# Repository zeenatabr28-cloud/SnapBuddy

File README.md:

# SnapBuddy
A retro 80's inspired Camera

WHY?
I want to be able to document Fallen and I can't actually affford a camera... So I am making one!

WHAT?
A cute retro style camera, with small touches that make it more personal/customisable, that only takes grainy, retro looking photos.

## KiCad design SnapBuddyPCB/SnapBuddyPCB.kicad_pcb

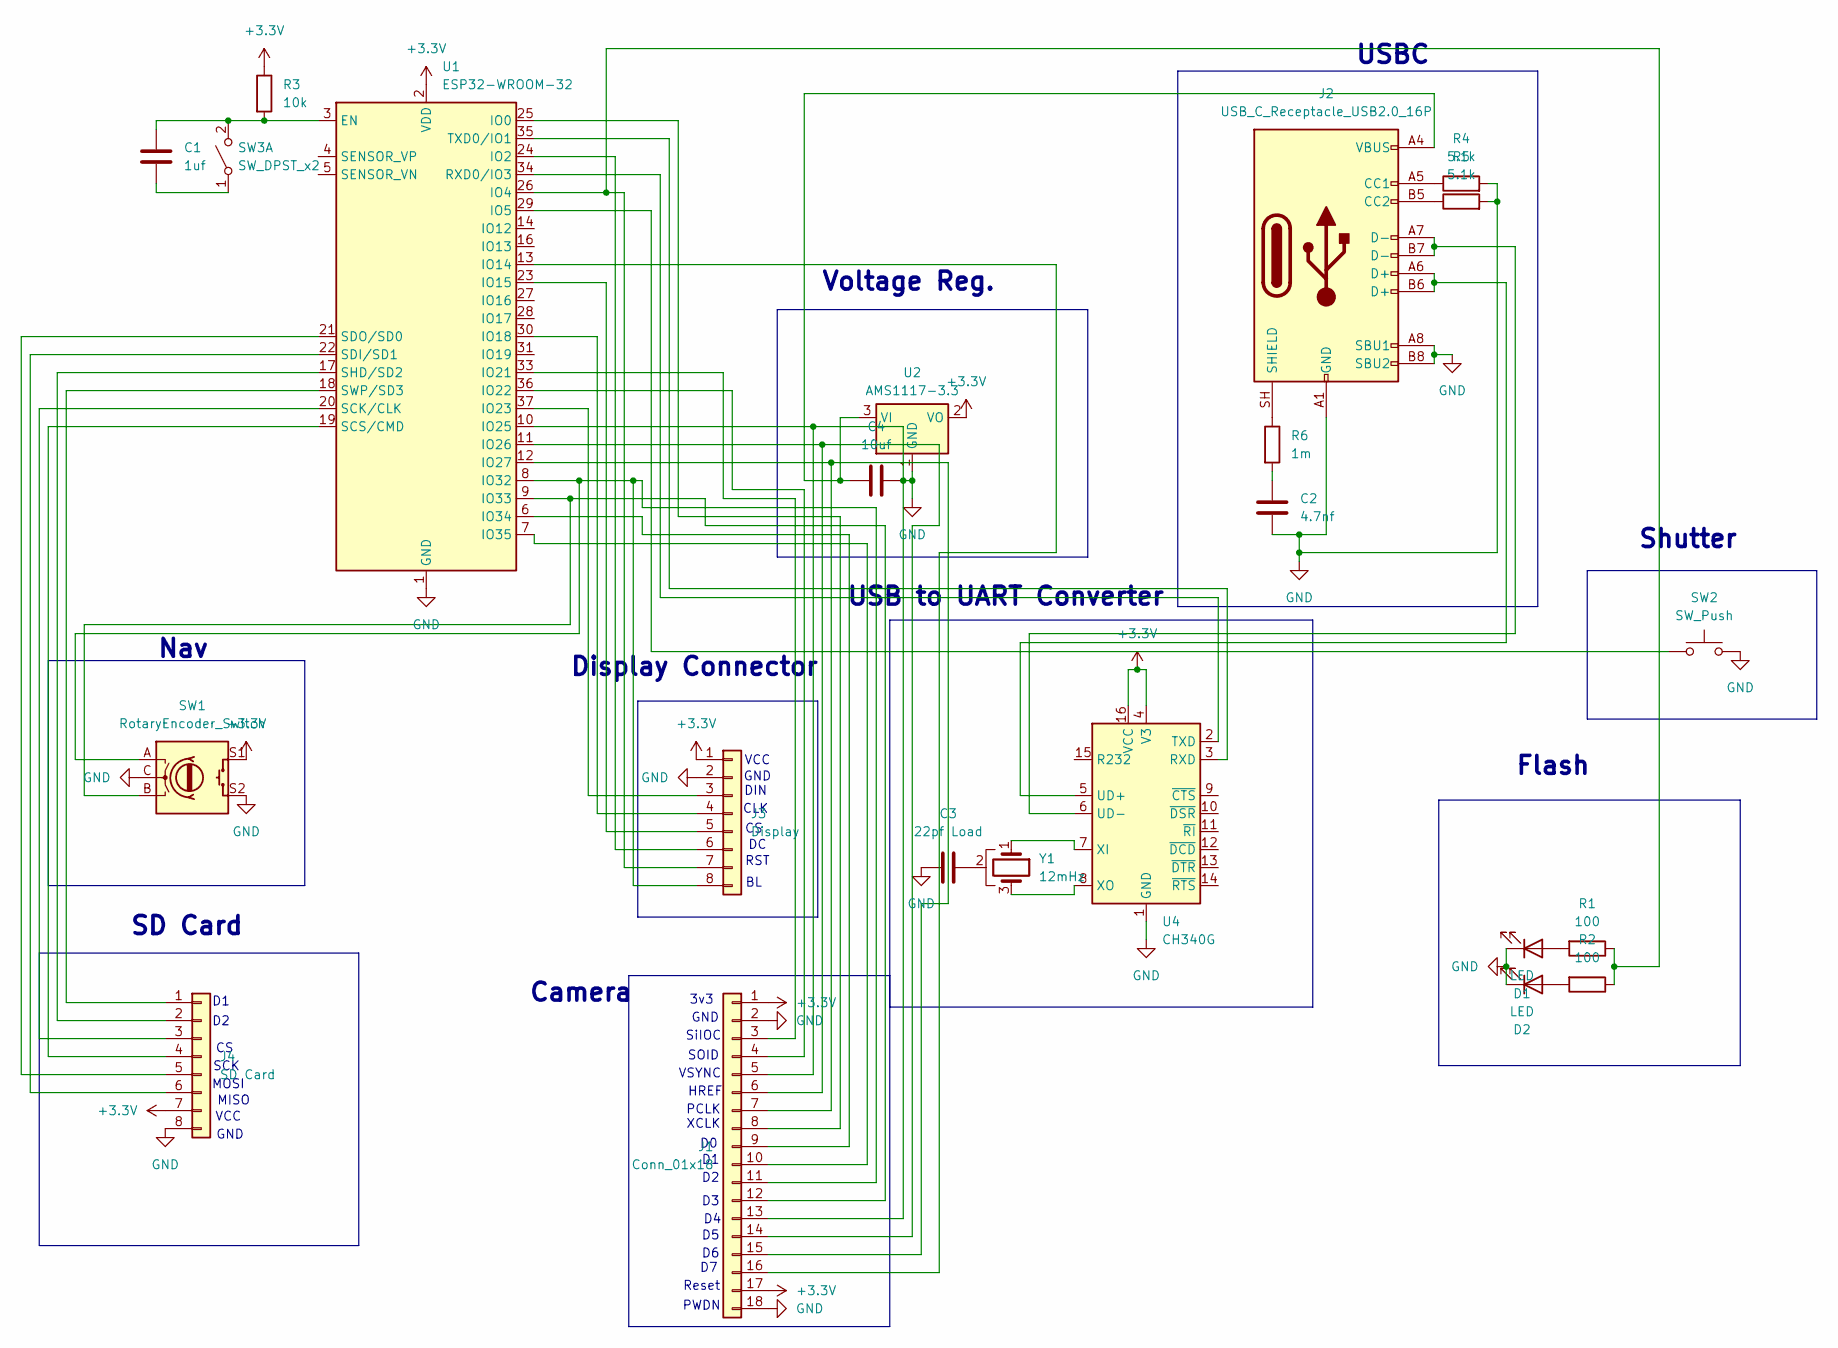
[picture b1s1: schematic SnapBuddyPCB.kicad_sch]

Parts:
C1: 1uf; CP_Elec_3x5.3
C2: 4.7nf; CP_Elec_3x5.3
C3: 22pf Load; CP_Elec_3x5.3
C4: 10uf; CP_Elec_3x5.3
D1, D2: LED; LED_D3.0mm
J1: Conn_01x18; PinSocket_1x18_P1.27mm_Vertical_SMD_Pin1Left
J2: USB_C_Receptacle_USB2.0_16P; USB_C_Receptacle_XKB_U262-16XN-4BVC11
J3: Display; PinSocket_1x08_P2.54mm_Vertical
J4: SD Card; PinSocket_1x08_P2.54mm_Vertical
R1, R2: 100; R_0603_1608Metric_Pad0.98x0.95mm_HandSolder
R3: 10k; R_0603_1608Metric_Pad0.98x0.95mm_HandSolder
R4, R5: 5.1k; R_0603_1608Metric_Pad0.98x0.95mm_HandSolder
R6: 1m; R_0603_1608Metric_Pad0.98x0.95mm_HandSolder
SW1: RotaryEncoder_Switch; RotaryEncoder_Bourns_Horizontal_PEC09-2xxxF-Sxxxx
SW2: SW_Push; SW_Push_1P1T_NO_CK_PTS125Sx85PSMTR
SW3: SW_DPST_x2; SW_Push_1P1T_NO_CK_PTS125Sx85PSMTR
U1: ESP32-WROOM-32
U2: AMS1117-3.3; SOT-223-3_TabPin2
U4: CH340G; SOIC-16_3.9x9.9mm_P1.27mm
Y1: 12mHz; Crystal_HC52-U-3Pin_Vertical

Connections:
+3.3V: J1.1, J1.17, J3.1, J4.7, R3.1, SW1.S1, U1.2 (VDD), U2.2 (VO), U4.4 (V3), U4.16 (VCC)
GND: C2.2, C3.2, C4.2, D1.1 (K), D2.1 (K), J1.2, J1.5, J1.13, J1.18, J2.A1 (GND), J2.A8 (SBU1), J2.A12 (GND), J2.B1 (GND), J2.B8 (SBU2), J2.B12 (GND), J3.2, J4.8, R4.2, R5.2, SW1.C, SW1.S2, SW2.2, U1.1 (GND), U1.10 (IO25), U1.15 (GND), U1.38 (GND), U1.39 (GND), U2.1 (GND), U4.1 (GND)
unnamed: C2.1, R6.2
unnamed: C3.1, Y1.2
unnamed: D1.2 (A), R1.2
unnamed: D2.2 (A), R2.2
unnamed: J1.3, U1.33 (IO21)
unnamed: J1.4, U1.36 (IO22)
unnamed: J1.8, U1.25 (IO0)
unnamed: J1.9, U1.6 (IO34)
unnamed: J1.10, U1.7 (IO35)
unnamed: J1.11, J3.8, SW1.A, U1.8 (IO32)
unnamed: J1.12, SW1.B, U1.9 (IO33)
unnamed: J1.6, J1.14, U1.11 (IO26)
unnamed: J1.7, J1.15, U1.12 (IO27)
unnamed: J1.16, U1.13 (IO14)
unnamed: J2.A5 (CC1), R4.1
unnamed: J2.B5 (CC2), R5.1
unnamed: J2.SH (SHIELD), R6.1
unnamed: J3.3, U1.37 (IO23)
unnamed: J3.4, U1.30 (IO18)
unnamed: J3.5, U1.23 (IO15)
unnamed: J3.6, U1.24 (IO2)
unnamed: J3.7, R1.1, R2.1, U1.26 (IO4)
unnamed: J4.1, U1.18 (SWP/SD3)
unnamed: J4.2, U1.17 (SHD/SD2)
unnamed: J4.3, U1.20 (SCK/CLK)
unnamed: J4.4, U1.19 (SCS/CMD)
unnamed: J4.5, U1.21 (SDO/SD0)
unnamed: J4.6, U1.22 (SDI/SD1)
unnamed: C1.2, SW3.1 (A)
unnamed: C1.1, R3.2, SW3.2 (B), U1.3 (EN)
unnamed: SW2.1, U1.29 (IO5)
unnamed: U1.34 (RXD0/IO3), U4.2 (TXD)
unnamed: U1.35 (TXD0/IO1), U4.3 (RXD)
unnamed: C4.1, J2.A4 (VBUS), J2.A9 (VBUS), J2.B4 (VBUS), J2.B9 (VBUS), U2.3 (VI)
unnamed: J2.A6 (D+), J2.B6 (D+), U4.5 (UD+)
unnamed: J2.A7 (D-), J2.B7 (D-), U4.6 (UD-)
unnamed: U4.7 (XI), Y1.1
unnamed: U4.8 (XO), Y1.3

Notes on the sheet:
Reset
VCC
GND
Camera
USBC
XCLK
DIN
CLK
MOSI
Nav
PWDN
RST
HREF
SOID
Flash
Display Connector
SD Card
VSYNC
SiIOC
MISO
3v3
SCK
PCLK
Shutter
USB to UART Converter
Voltage Reg.

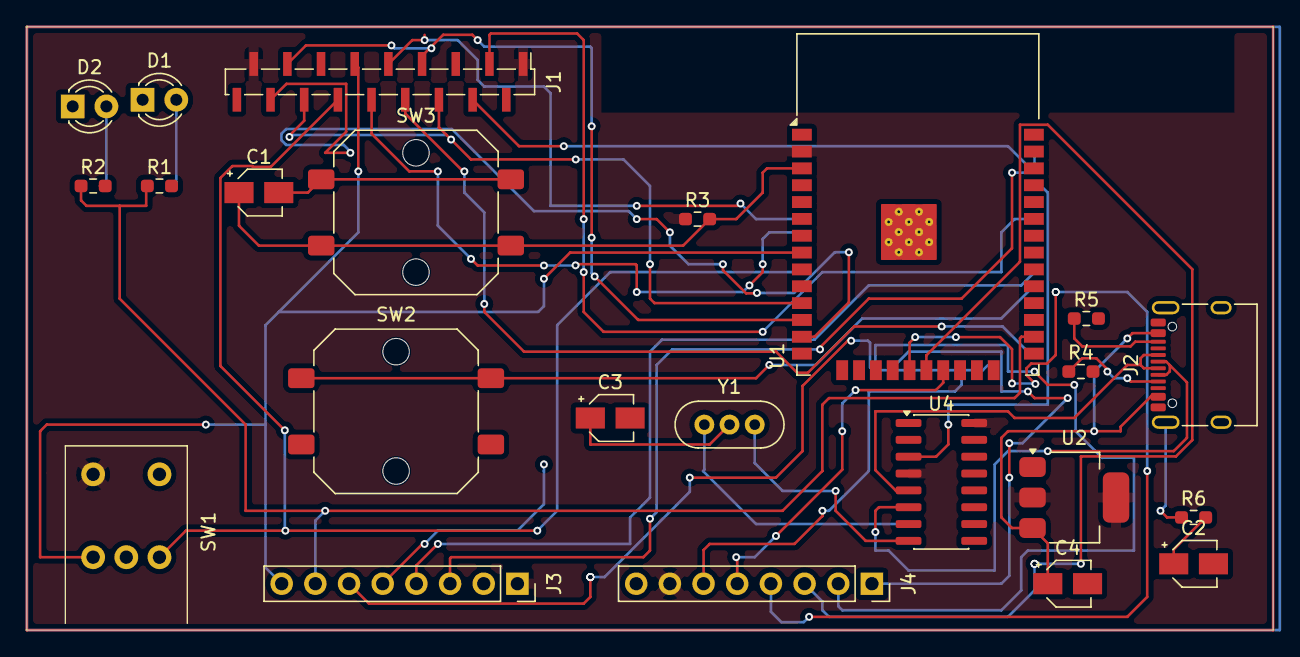
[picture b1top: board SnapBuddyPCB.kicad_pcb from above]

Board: 2 copper layers, 94.0 x 45.5 mm, 23 parts (0 on the bottom side), 40 nets.
